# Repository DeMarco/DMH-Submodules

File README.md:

# DMH-Submodules
Collection of small plugin PCBs used as subcircuits in major Kosmo modules

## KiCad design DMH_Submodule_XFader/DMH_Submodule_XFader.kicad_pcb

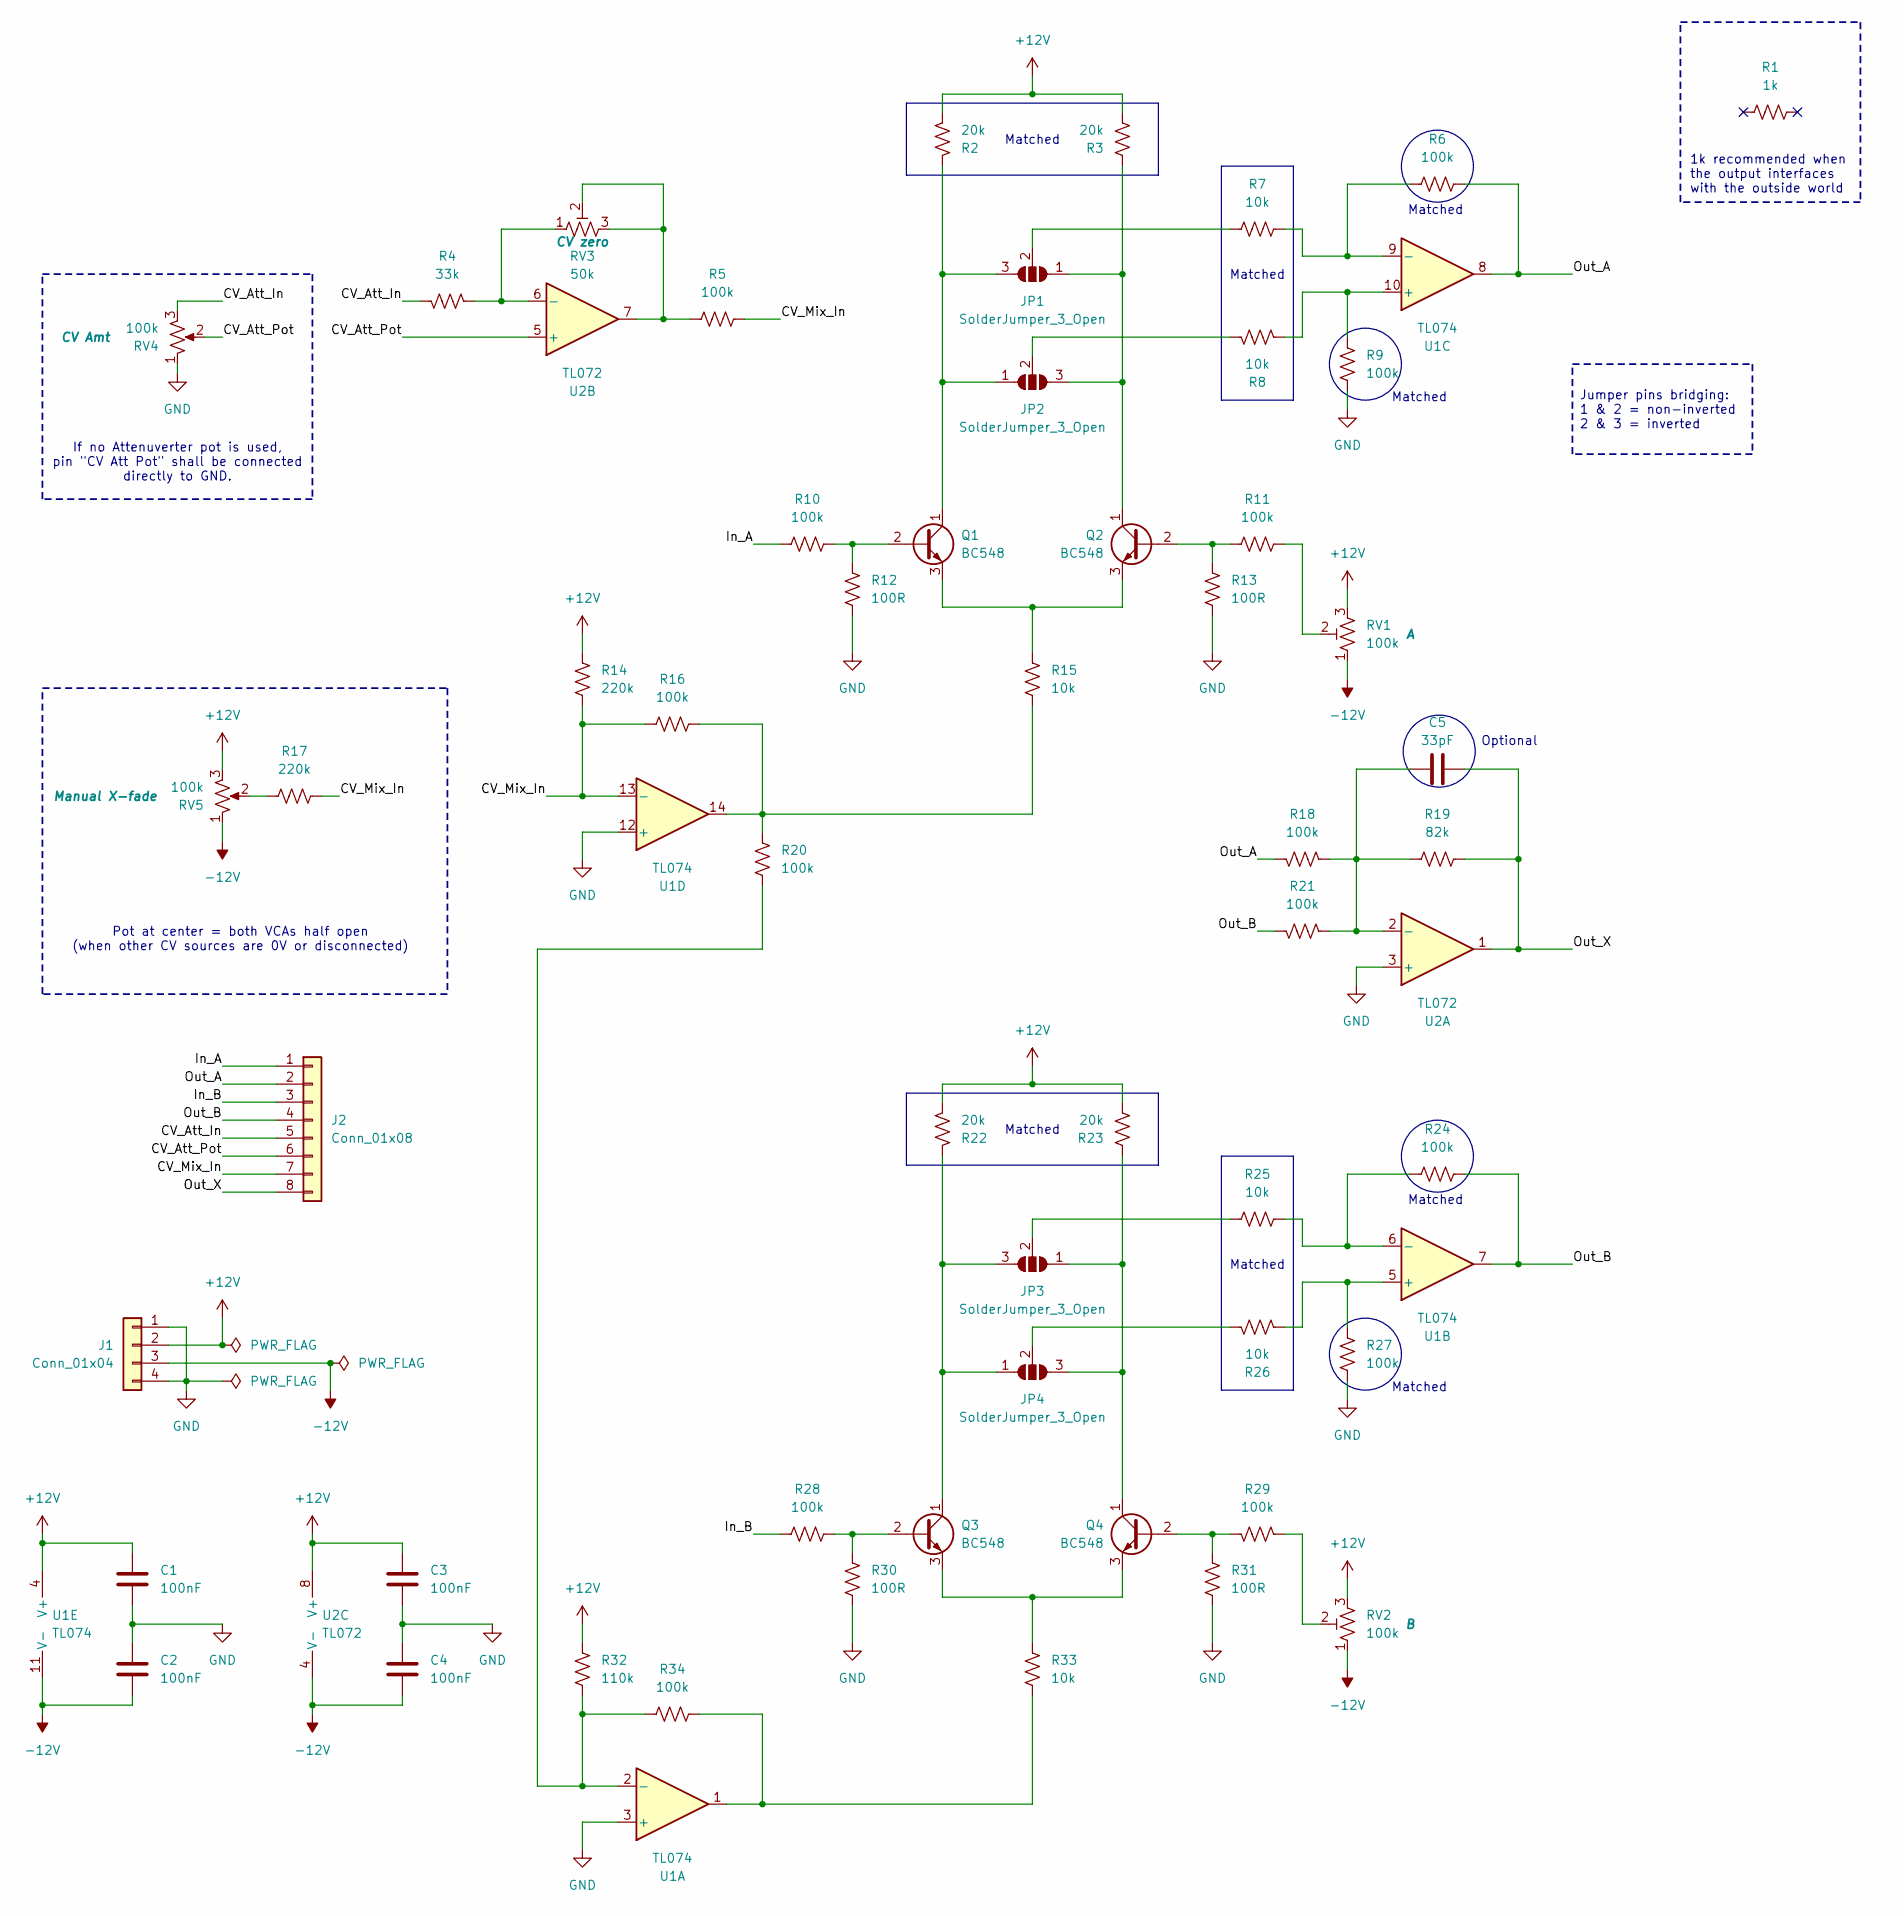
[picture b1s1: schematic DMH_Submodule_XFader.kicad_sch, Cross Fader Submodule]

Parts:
C1, C2, C3, C4: 100nF; C_Disc_D4.3mm_W1.9mm_P5.00mm
C5: 33pF; C_Disc_D3.0mm_W2.0mm_P2.50mm
J1: Conn_01x04; PinHeader_1x04_P2.54mm_Horizontal
J2: Conn_01x08; PinHeader_1x08_P2.54mm_Horizontal
JP1, JP2, JP3, JP4: SolderJumper_3_Open; SolderJumper-3_P1.3mm_Open_RoundedPad1.0x1.5mm_NumberLabels
Q1, Q2, Q3, Q4: BC548; TO-92L_Inline_Wide
R1: 1k; R_Axial_DIN0207_L6.3mm_D2.5mm_P7.62mm_Horizontal
R2, R3, R22, R23: 20k; R_Axial_DIN0207_L6.3mm_D2.5mm_P2.54mm_Vertical
R4: 33k; R_Axial_DIN0207_L6.3mm_D2.5mm_P2.54mm_Vertical
R5, R6, R9, R10, R11, R16, R18, R20, R21, R24, R27, R28, R29, R34: 100k; R_Axial_DIN0207_L6.3mm_D2.5mm_P2.54mm_Vertical
R7, R8, R15, R25, R26, R33: 10k; R_Axial_DIN0207_L6.3mm_D2.5mm_P2.54mm_Vertical
R12, R13, R30, R31: 100R; R_Axial_DIN0207_L6.3mm_D2.5mm_P2.54mm_Vertical
R14: 220k; R_Axial_DIN0207_L6.3mm_D2.5mm_P2.54mm_Vertical
R17: 220k; R_Axial_DIN0207_L6.3mm_D2.5mm_P7.62mm_Horizontal
R19: 82k; R_Axial_DIN0207_L6.3mm_D2.5mm_P2.54mm_Vertical
R32: 110k; R_Axial_DIN0207_L6.3mm_D2.5mm_P2.54mm_Vertical
RV1, RV2: 100k; Potentiometer_Bourns_3296X_Horizontal
RV3: 50k; Potentiometer_Bourns_3296X_Horizontal
RV4, RV5: 100k; Potentiometer_TT_P110KH1
U1: TL074; DIP-14_W7.62mm_Socket
U2: TL072; DIP-8_W7.62mm_Socket

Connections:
+12V: C1.1, C3.1, J1.2, R2.1, R3.1, R14.2, R22.1, R23.1, R32.2, RV1.3, RV2.3, RV5.3, U1.4 (V+), U2.8 (V+)
-12V: C2.2, C4.2, J1.3, RV1.1, RV2.1, RV5.1, U1.11 (V-), U2.4 (V-)
/CV_Att_In: J2.5, R4.2, RV4.3
/CV_Att_Pot: J2.6, RV4.2, U2.5 (+)
/CV_Mix_In: J2.7, R5.1, R14.1, R16.1, R17.2, U1.13 (-)
/In_A: J2.1, R10.2
/In_B: J2.3, R28.2
/Out_A: J2.2, R6.1, R18.2, U1.8
/Out_B: J2.4, R21.2, R24.1, U1.7
/Out_X: C5.2, J2.8, R19.2, U2.1
GND: C1.2, C2.1, C3.2, C4.1, J1.1, J1.4, R9.2, R12.1, R13.1, R27.2, R30.1, R31.1, RV4.1, U1.3 (+), U1.12 (+), U2.3 (+)
unnamed: JP1.1 (A), JP2.3 (B), Q2.1 (C), R3.2
unnamed: JP1.3 (B), JP2.1 (A), Q1.1 (C), R2.2
unnamed: JP1.2 (C), R7.2
unnamed: JP2.2 (C), R8.2
unnamed: JP3.1 (A), JP4.3 (B), Q4.1 (C), R23.2
unnamed: JP3.3 (B), JP4.1 (A), Q3.1 (C), R22.2
unnamed: JP3.2 (C), R25.2
unnamed: JP4.2 (C), R26.2
unnamed: Q1.2 (B), R10.1, R12.2
unnamed: Q1.3 (E), Q2.3 (E), R15.2
unnamed: Q2.2 (B), R11.2, R13.2
unnamed: Q3.2 (B), R28.1, R30.2
unnamed: Q3.3 (E), Q4.3 (E), R33.2
unnamed: Q4.2 (B), R29.1, R31.2
unnamed: R5.2, RV3.2, RV3.3, U2.7
unnamed: R11.1, RV1.2
unnamed: R15.1, R16.2, R20.2, U1.14
unnamed: R17.1, RV5.2
unnamed: R29.2, RV2.2
unnamed: R33.1, R34.2, U1.1
unnamed: R20.1, R32.1, R34.1, U1.2 (-)
unnamed: R26.1, R27.1, U1.5 (+)
unnamed: R24.2, R25.1, U1.6 (-)
unnamed: R8.1, R9.1, U1.10 (+)
unnamed: R6.2, R7.1, U1.9 (-)
unnamed: C5.1, R18.1, R19.1, R21.1, U2.2 (-)
unnamed: R4.1, RV3.1, U2.6 (-)

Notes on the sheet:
Matched
If no Attenuverter pot is used, pin "CV Att Pot" shall be connected directly to GND.
1k recommended when the output interfaces with the outside world
Pot at center = both VCAs half open (when other CV sources are 0V or disconnected)
Optional
Jumper pins bridging: 1 & 2 = non-inverted 2 & 3 = inverted

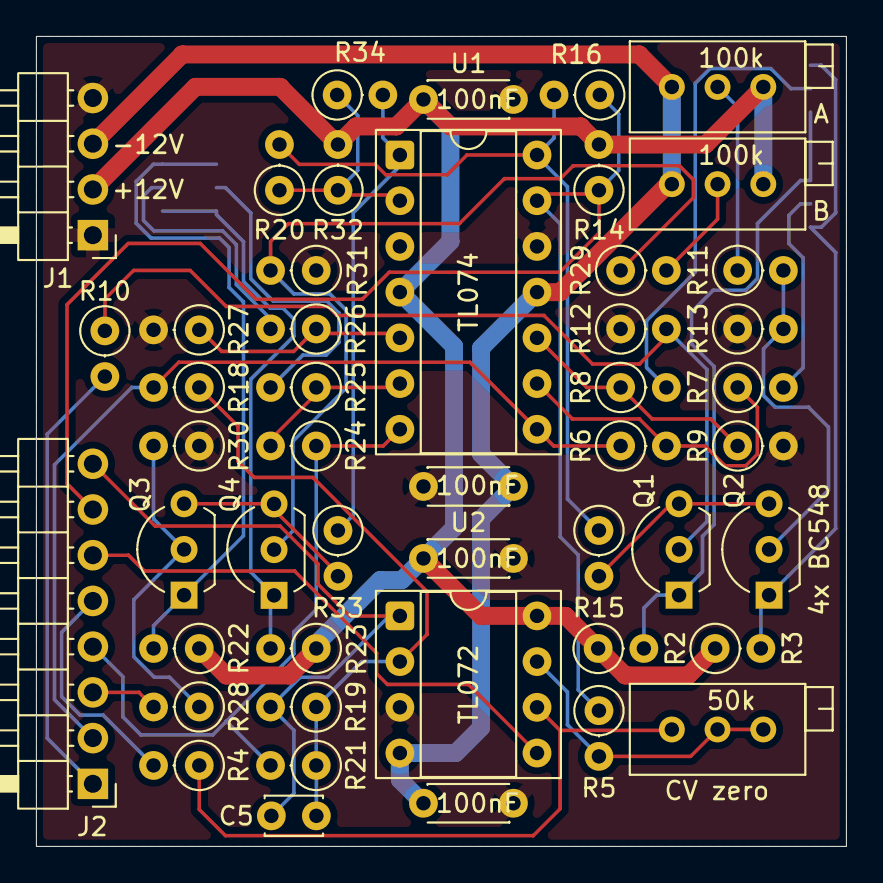
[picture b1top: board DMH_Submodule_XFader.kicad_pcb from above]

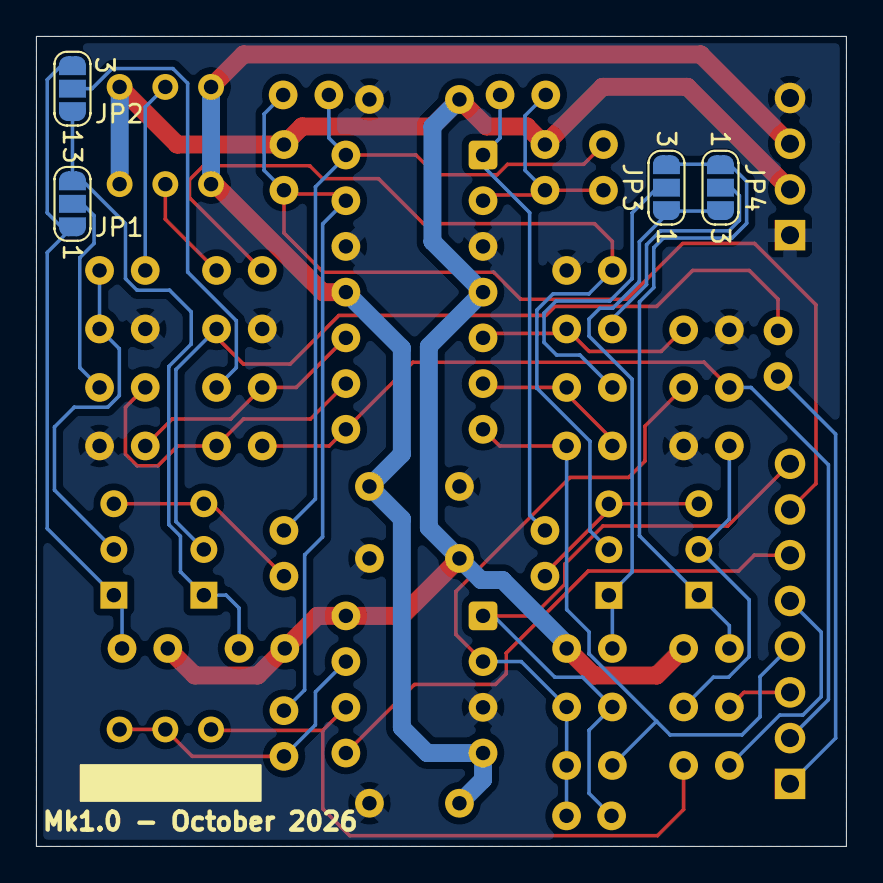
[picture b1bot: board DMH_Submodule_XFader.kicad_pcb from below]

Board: 2 copper layers, 45.0 x 45.0 mm, 52 parts (4 on the bottom side), 37 nets.

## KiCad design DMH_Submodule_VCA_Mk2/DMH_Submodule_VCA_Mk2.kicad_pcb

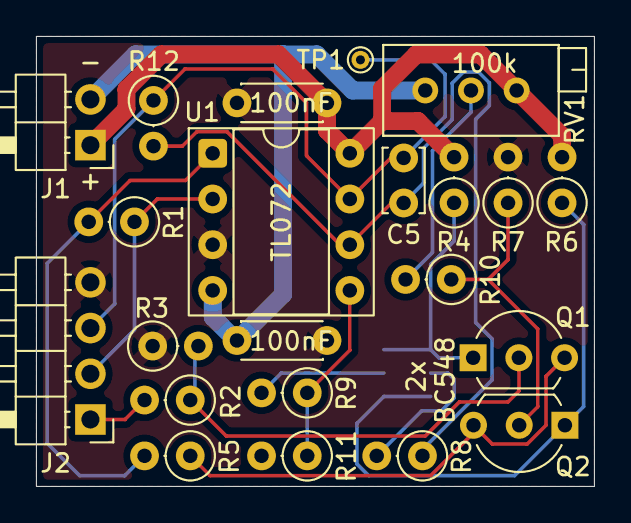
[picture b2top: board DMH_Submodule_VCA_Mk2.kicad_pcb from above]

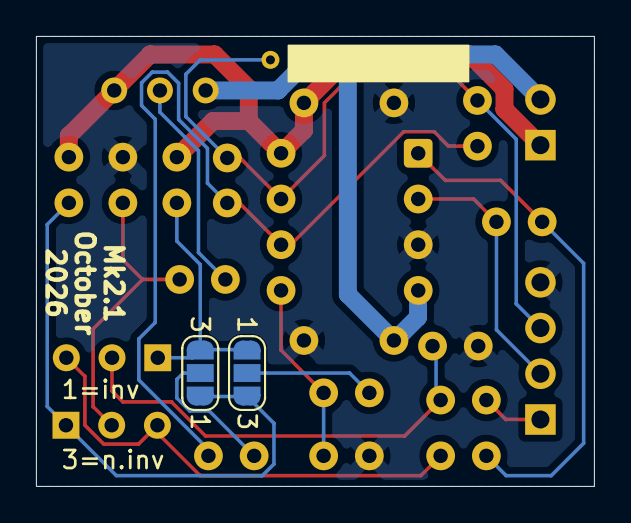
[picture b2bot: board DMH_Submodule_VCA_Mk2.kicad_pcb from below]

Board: 2 copper layers, 31.0 x 25.0 mm, 24 parts (2 on the bottom side), 17 nets.

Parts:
C1, C2: 100nF; C_Disc_D4.3mm_W1.9mm_P5.00mm
C5: 33pF; C_Disc_D3.4mm_W2.1mm_P2.50mm
J1: Conn_01x02; PinHeader_1x02_P2.54mm_Horizontal
J2: Conn_01x04; PinHeader_1x04_P2.54mm_Horizontal
JP1, JP2: SolderJumper_3_Open; SolderJumper-3_P1.3mm_Open_RoundedPad1.0x1.5mm_NumberLabels
Q1, Q2: BC548; TO-92L_Inline_Wide
R1, R2, R10, R11, R12: 100k; R_Axial_DIN0207_L6.3mm_D2.5mm_P2.54mm_Vertical
R3, R7: 100R; R_Axial_DIN0207_L6.3mm_D2.5mm_P2.54mm_Vertical
R4, R6: 20k; R_Axial_DIN0207_L6.3mm_D2.5mm_P2.54mm_Vertical
R5, R8, R9: 10k; R_Axial_DIN0207_L6.3mm_D2.5mm_P2.54mm_Vertical
RV1: 100k; Potentiometer_Bourns_3296X_Horizontal
TP1: TestPoint_Probe; TestPoint_THTPad_D1.0mm_Drill0.5mm
U1: TL072; DIP-8_W7.62mm_Socket

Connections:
+12V: C1.1, J1.1, R4.2, R6.2, RV1.3, U1.8 (V+)
-12V: C2.2, J1.2, RV1.1, U1.4 (V-)
/CV_Mix_In: J2.2, R1.1, U1.2 (-)
/Signal_In: J2.1, R2.2
/Signal_Out: C5.2, J2.3, R12.1, TP1.1 (1_1), U1.7
GND: C1.2, C2.1, J2.4, R3.1, R7.2, R11.2, U1.3 (+)
unnamed: JP1.1 (A), JP2.3 (B), Q2.1 (C), R6.1
unnamed: JP1.3 (B), JP2.1 (A), Q1.1 (C), R4.1
unnamed: JP1.2 (C), R8.2
unnamed: JP2.2 (C), R9.2
unnamed: Q1.2 (B), R2.1, R3.2
unnamed: Q1.3 (E), Q2.3 (E), R5.1
unnamed: Q2.2 (B), R7.1, R10.1
unnamed: R1.2, R5.2, U1.1
unnamed: R10.2, RV1.2
unnamed: R9.1, R11.1, U1.5 (+)
unnamed: C5.1, R8.1, R12.2, U1.6 (-)

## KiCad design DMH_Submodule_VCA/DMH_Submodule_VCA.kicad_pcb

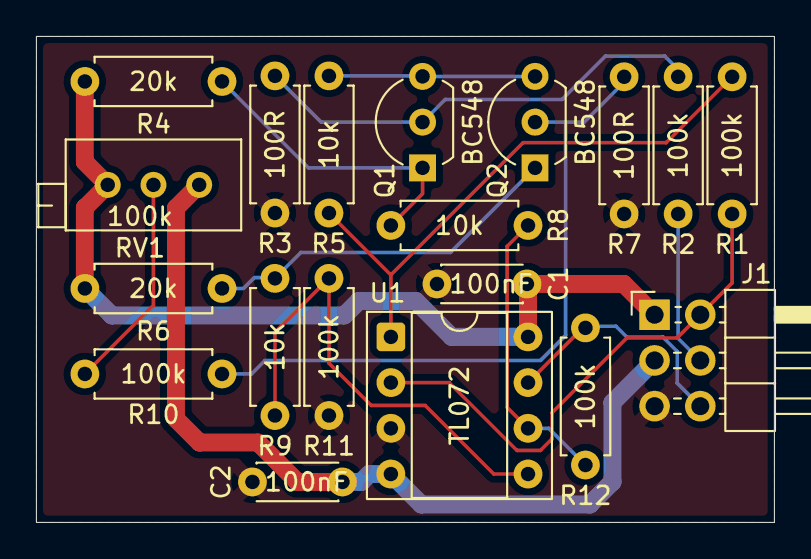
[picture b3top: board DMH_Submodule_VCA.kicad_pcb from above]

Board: 2 copper layers, 41.0 x 27.0 mm, 19 parts (0 on the bottom side), 15 nets.

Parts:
C1, C2: 100nF; C_Disc_D4.3mm_W1.9mm_P5.00mm
J1: Conn_02x03_Odd_Even; PinHeader_2x03_P2.54mm_Horizontal
Q1, Q2: BC548; TO-92L_Inline_Wide
R1, R2, R10, R11, R12: 100k; R_Axial_DIN0207_L6.3mm_D2.5mm_P7.62mm_Horizontal
R3, R7: 100R; R_Axial_DIN0207_L6.3mm_D2.5mm_P7.62mm_Horizontal
R4, R6: 20k; R_Axial_DIN0207_L6.3mm_D2.5mm_P7.62mm_Horizontal
R5, R8, R9: 10k; R_Axial_DIN0207_L6.3mm_D2.5mm_P7.62mm_Horizontal
RV1: 100k; Potentiometer_Bourns_3296X_Horizontal
U1: TL072; DIP-8_W7.62mm_Socket

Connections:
+12V: C1.1, J1.1, R4.2, R6.2, RV1.3, U1.8 (V+)
-12V: C2.2, J1.3, RV1.1, U1.4 (V-)
/CV Mix In: J1.2, R1.1, U1.2 (-)
/Signal In: J1.4, R2.2
/Signal Out: J1.6, R12.1, U1.7
GND: C1.2, C2.1, J1.5, R3.1, R7.1, R11.2, U1.3 (+)
unnamed: Q1.2 (B), R2.1, R3.2
unnamed: Q1.1 (C), R4.1, R8.2
unnamed: Q1.3 (E), Q2.3 (E), R5.2
unnamed: Q2.2 (B), R7.2, R10.2
unnamed: Q2.1 (C), R6.1, R9.2
unnamed: R1.2, R5.1, U1.1
unnamed: R10.1, RV1.2
unnamed: R9.1, R11.1, U1.5 (+)
unnamed: R8.1, R12.2, U1.6 (-)

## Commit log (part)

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2026-03-23 VCA submodule PCB design in progress
2026-04-18 Designed PCB
2026-04-19 Derived VCA design blocks
2026-05-30 Update SynthStuff
2026-06-20 Generated VCA gerbers
2026-06-25 Corrected VCA gerber zip file name
2026-06-28 Started Xfader project and done simulation
2026-06-28 Designed X fader schematic
2026-06-28 Xfader comp placement in progress
